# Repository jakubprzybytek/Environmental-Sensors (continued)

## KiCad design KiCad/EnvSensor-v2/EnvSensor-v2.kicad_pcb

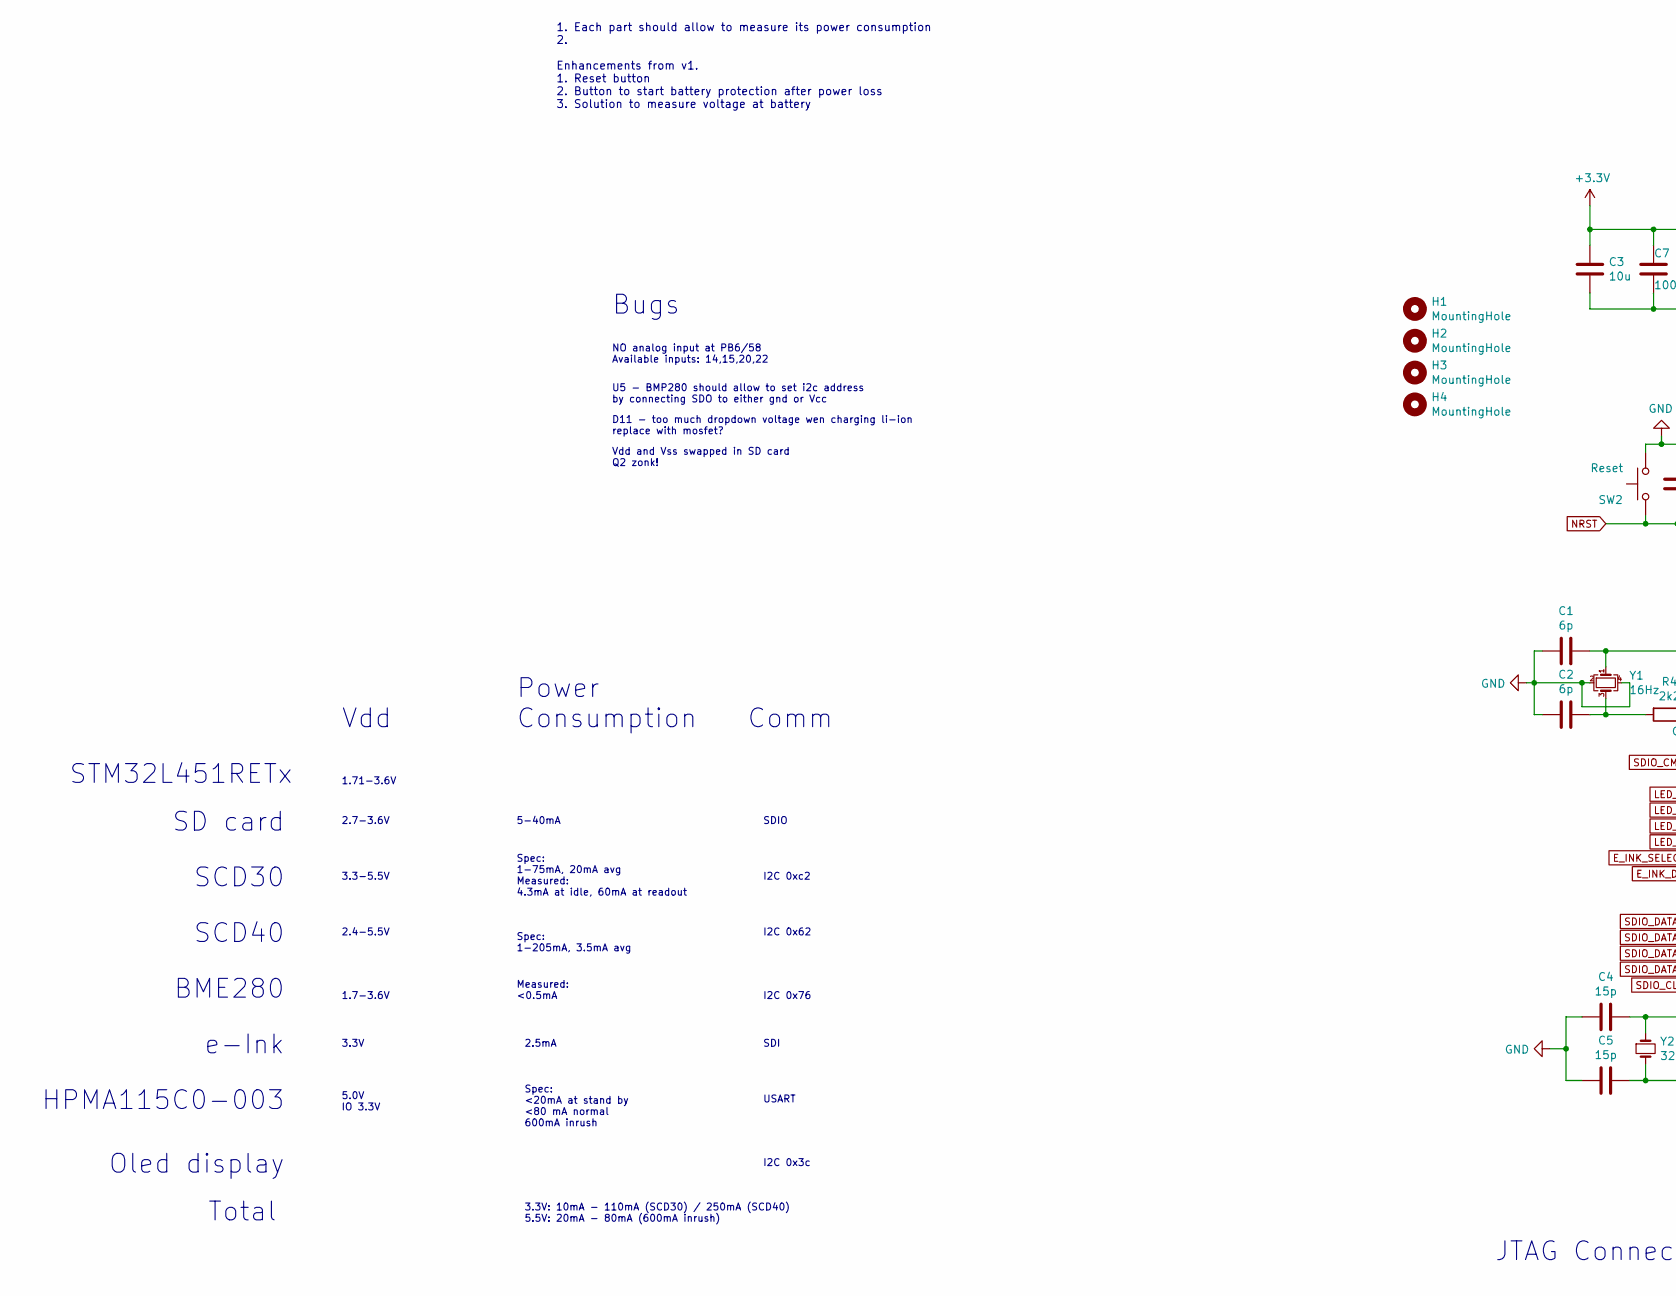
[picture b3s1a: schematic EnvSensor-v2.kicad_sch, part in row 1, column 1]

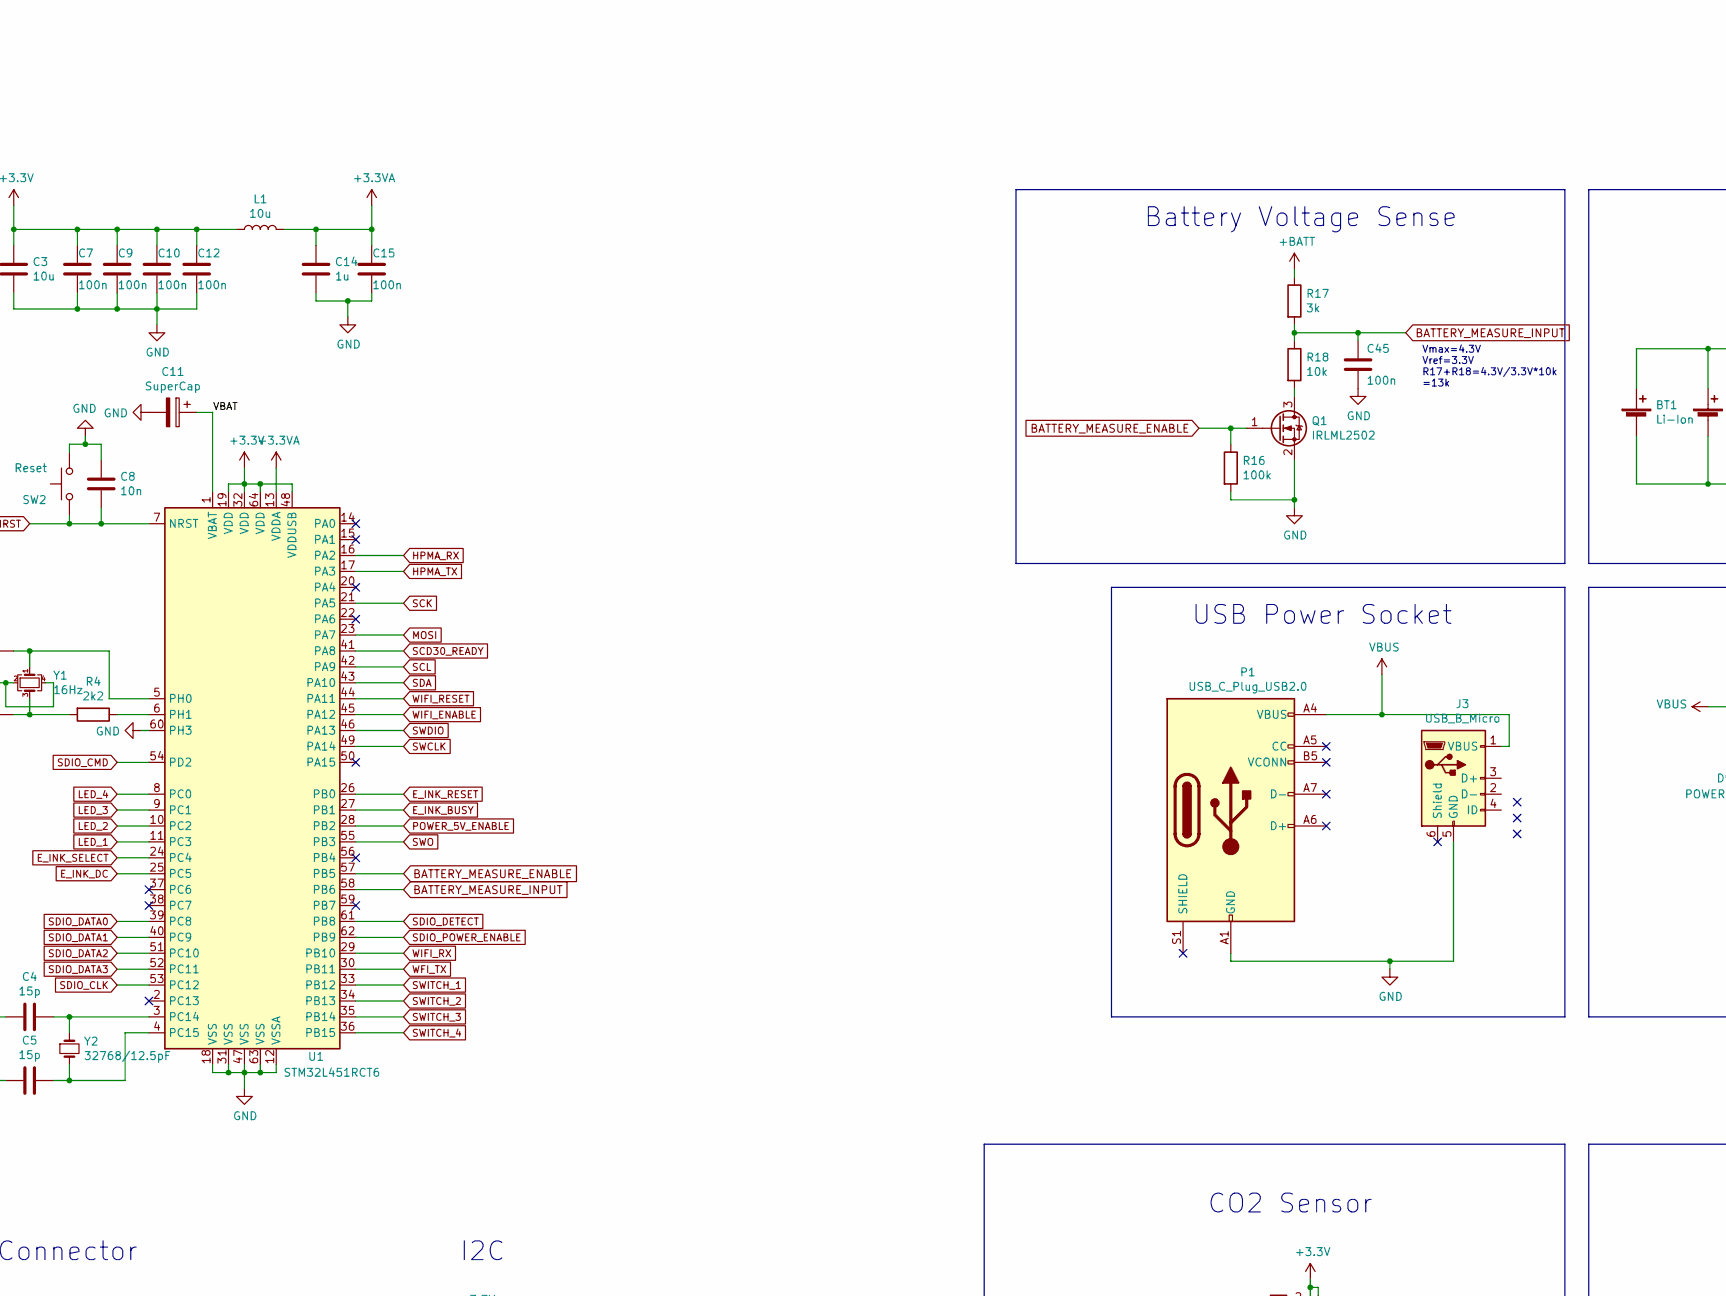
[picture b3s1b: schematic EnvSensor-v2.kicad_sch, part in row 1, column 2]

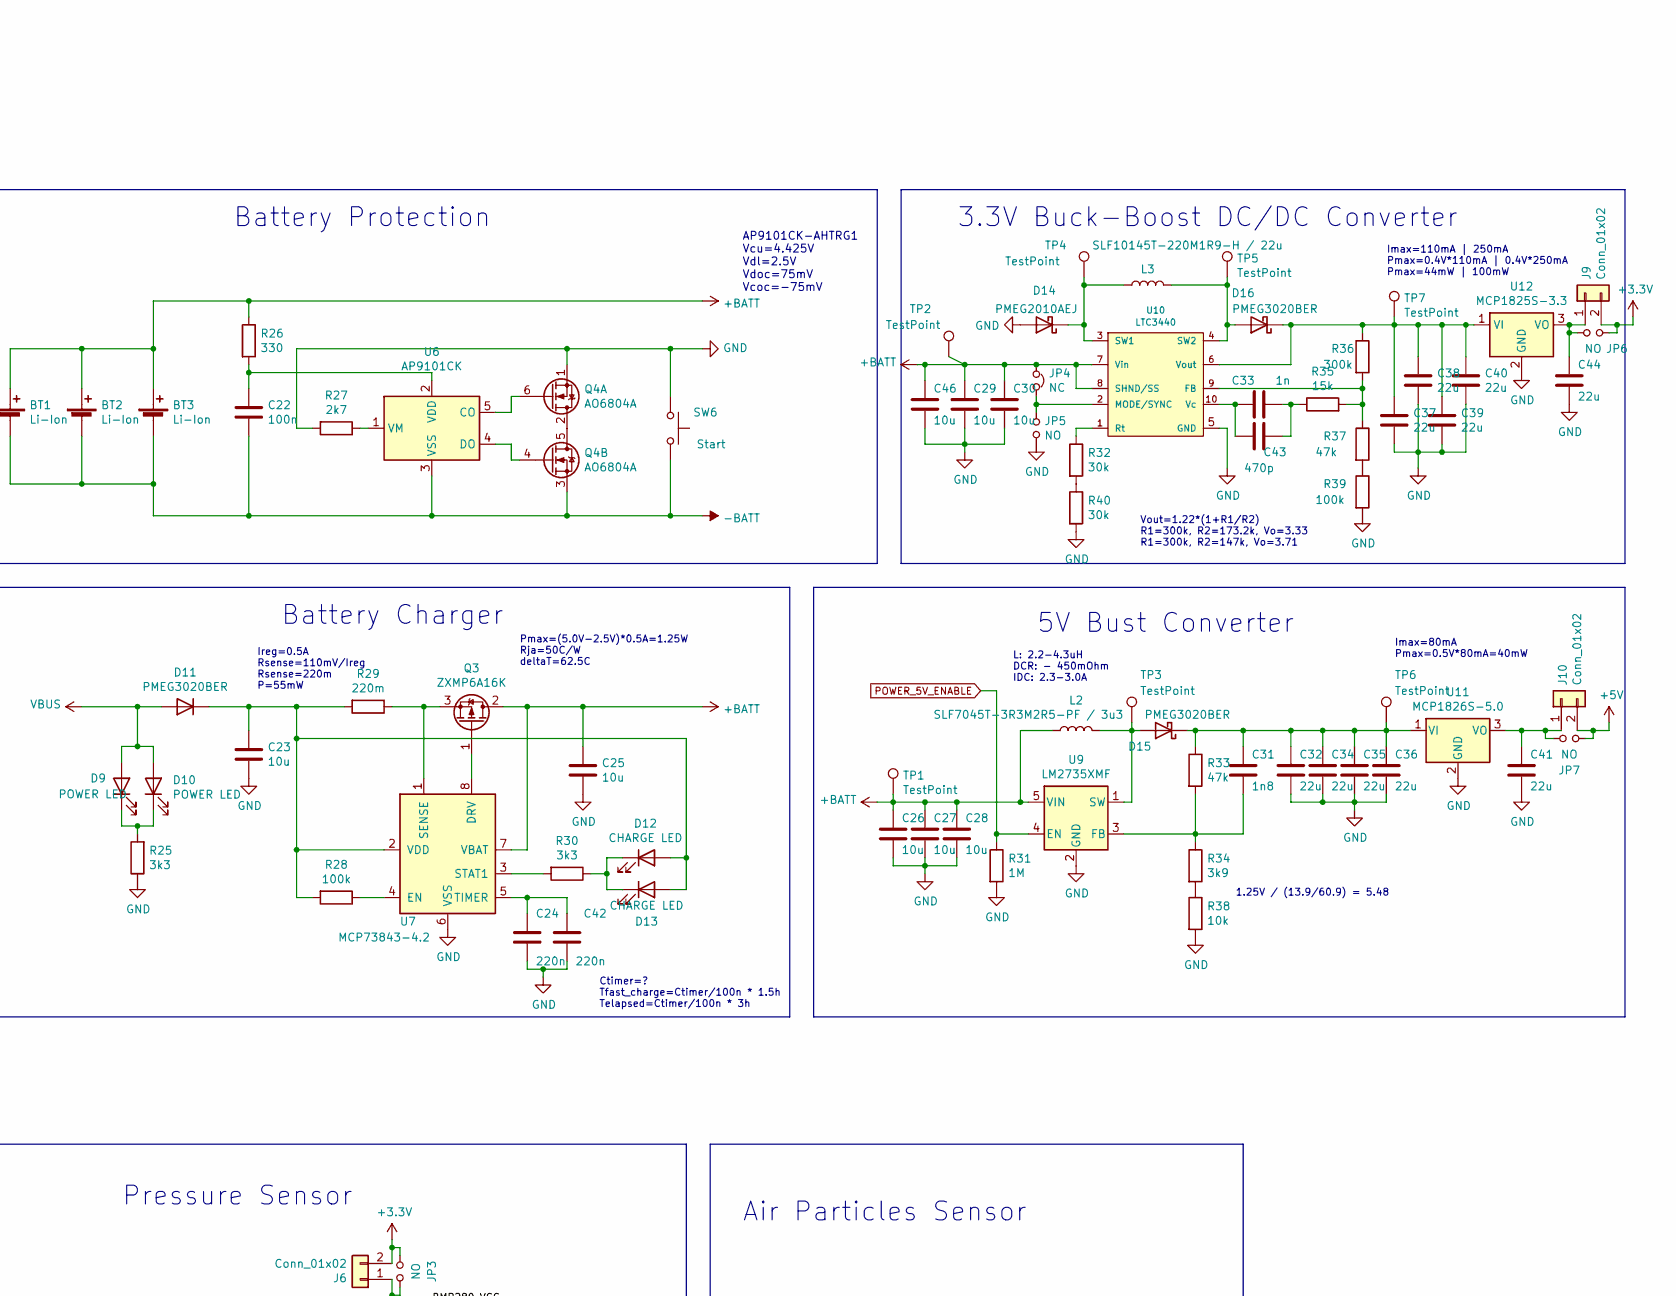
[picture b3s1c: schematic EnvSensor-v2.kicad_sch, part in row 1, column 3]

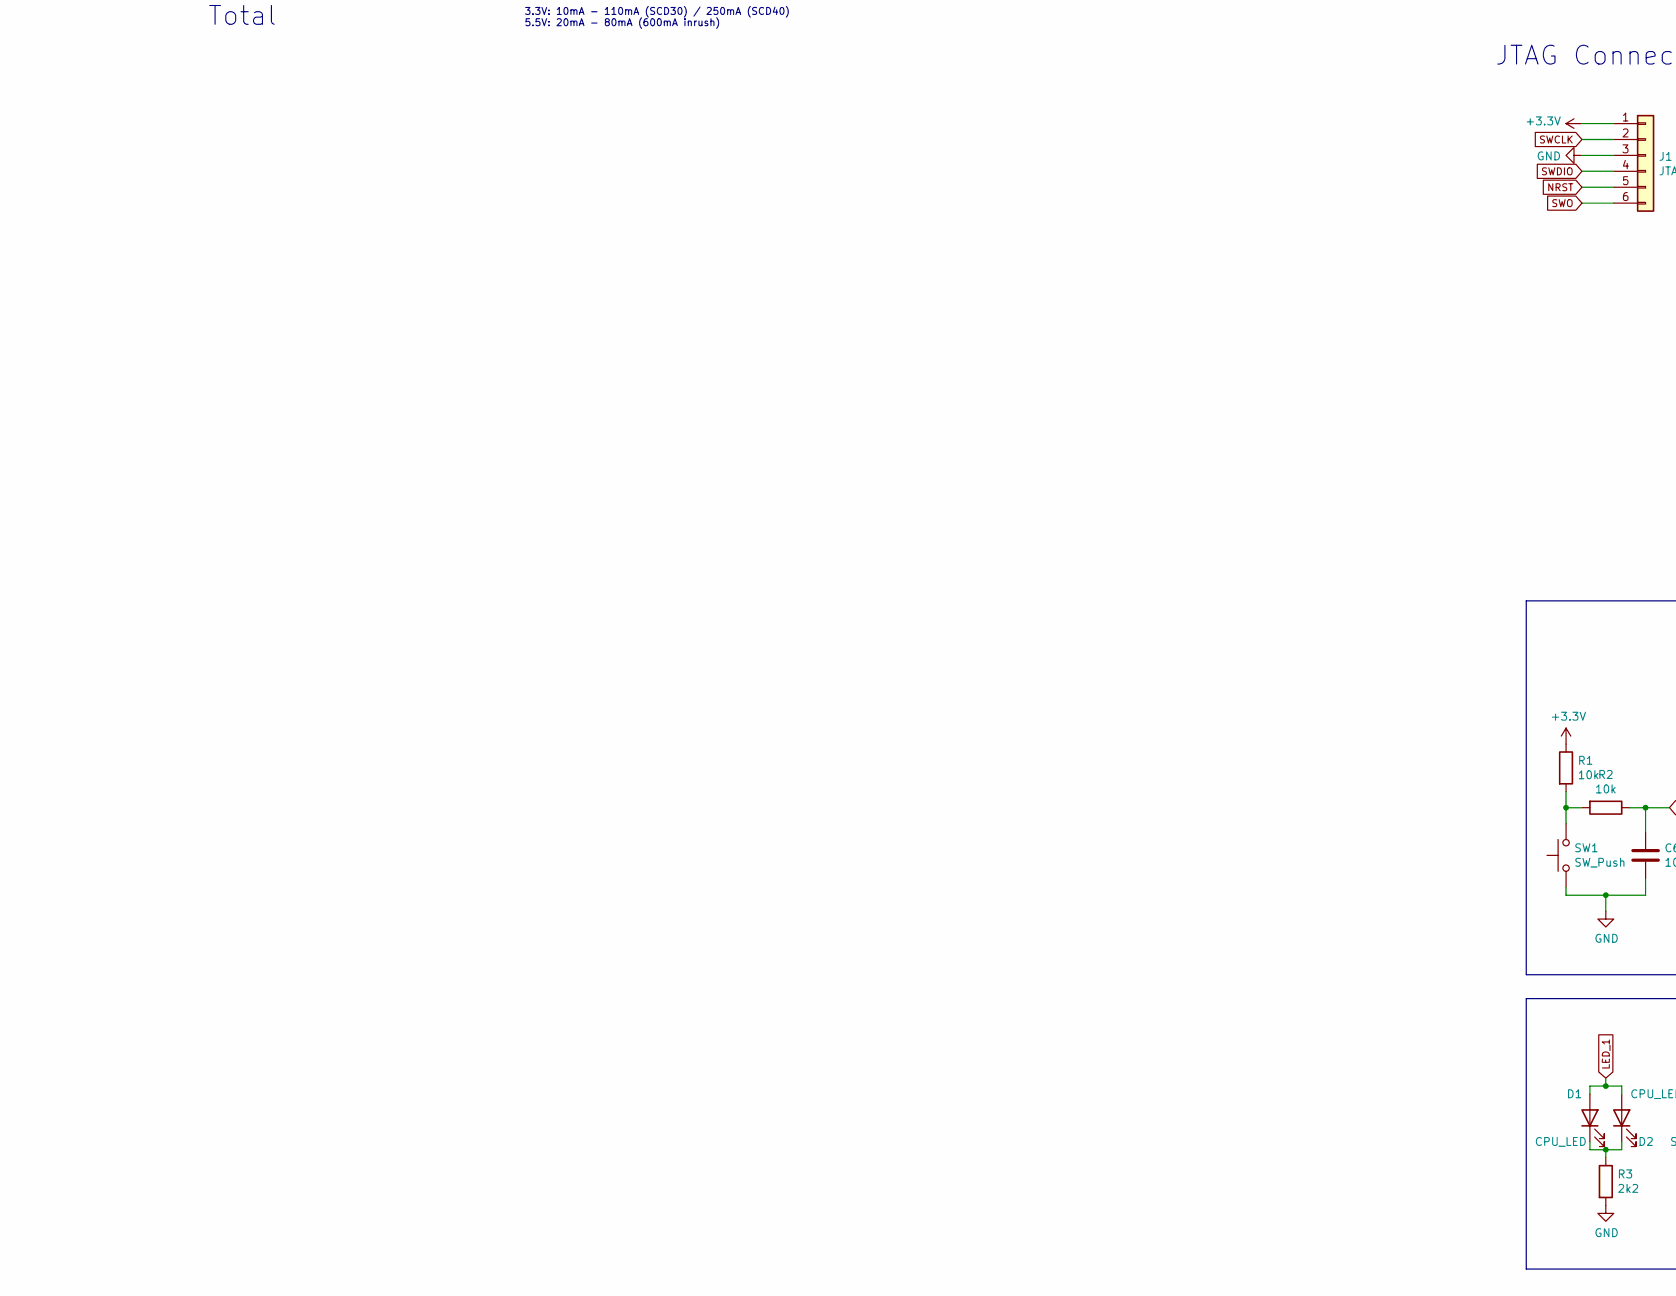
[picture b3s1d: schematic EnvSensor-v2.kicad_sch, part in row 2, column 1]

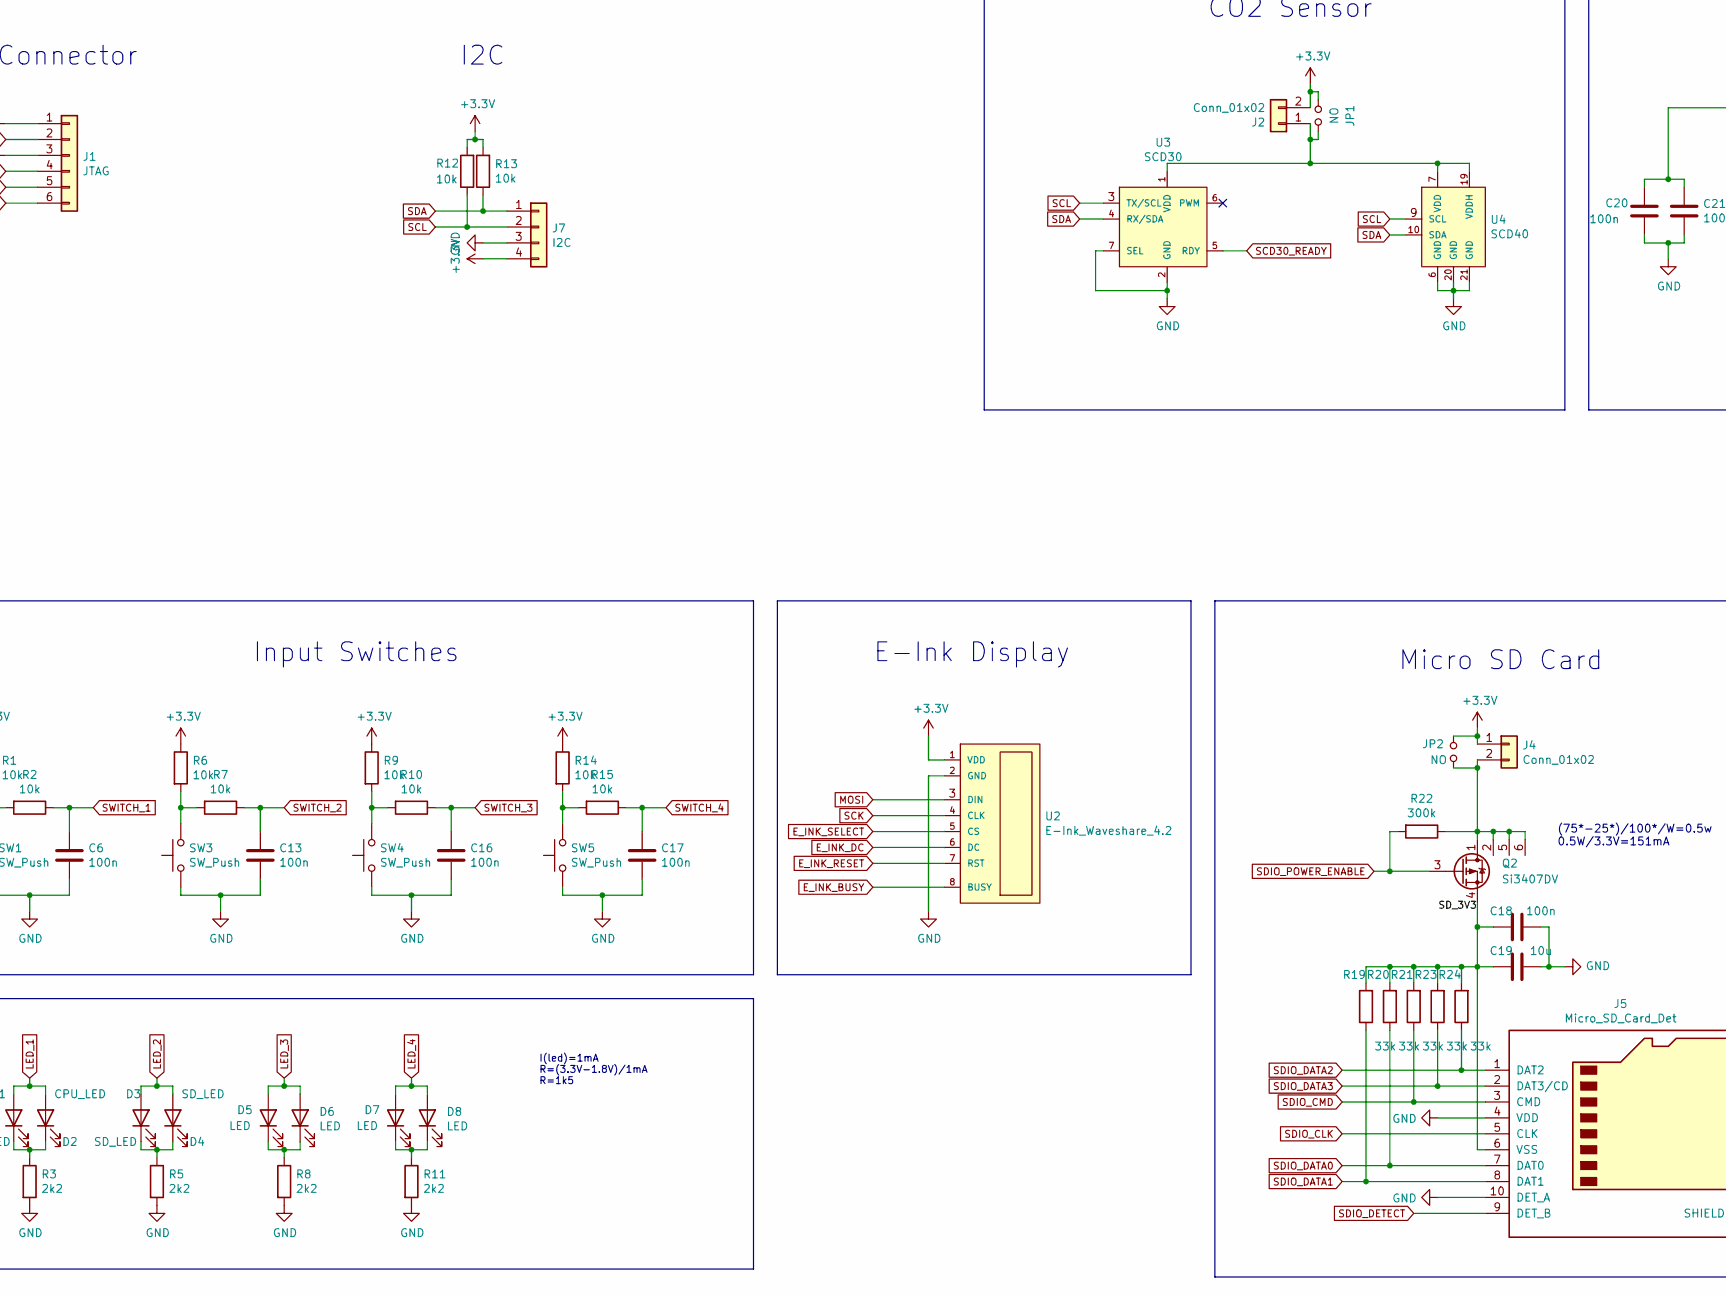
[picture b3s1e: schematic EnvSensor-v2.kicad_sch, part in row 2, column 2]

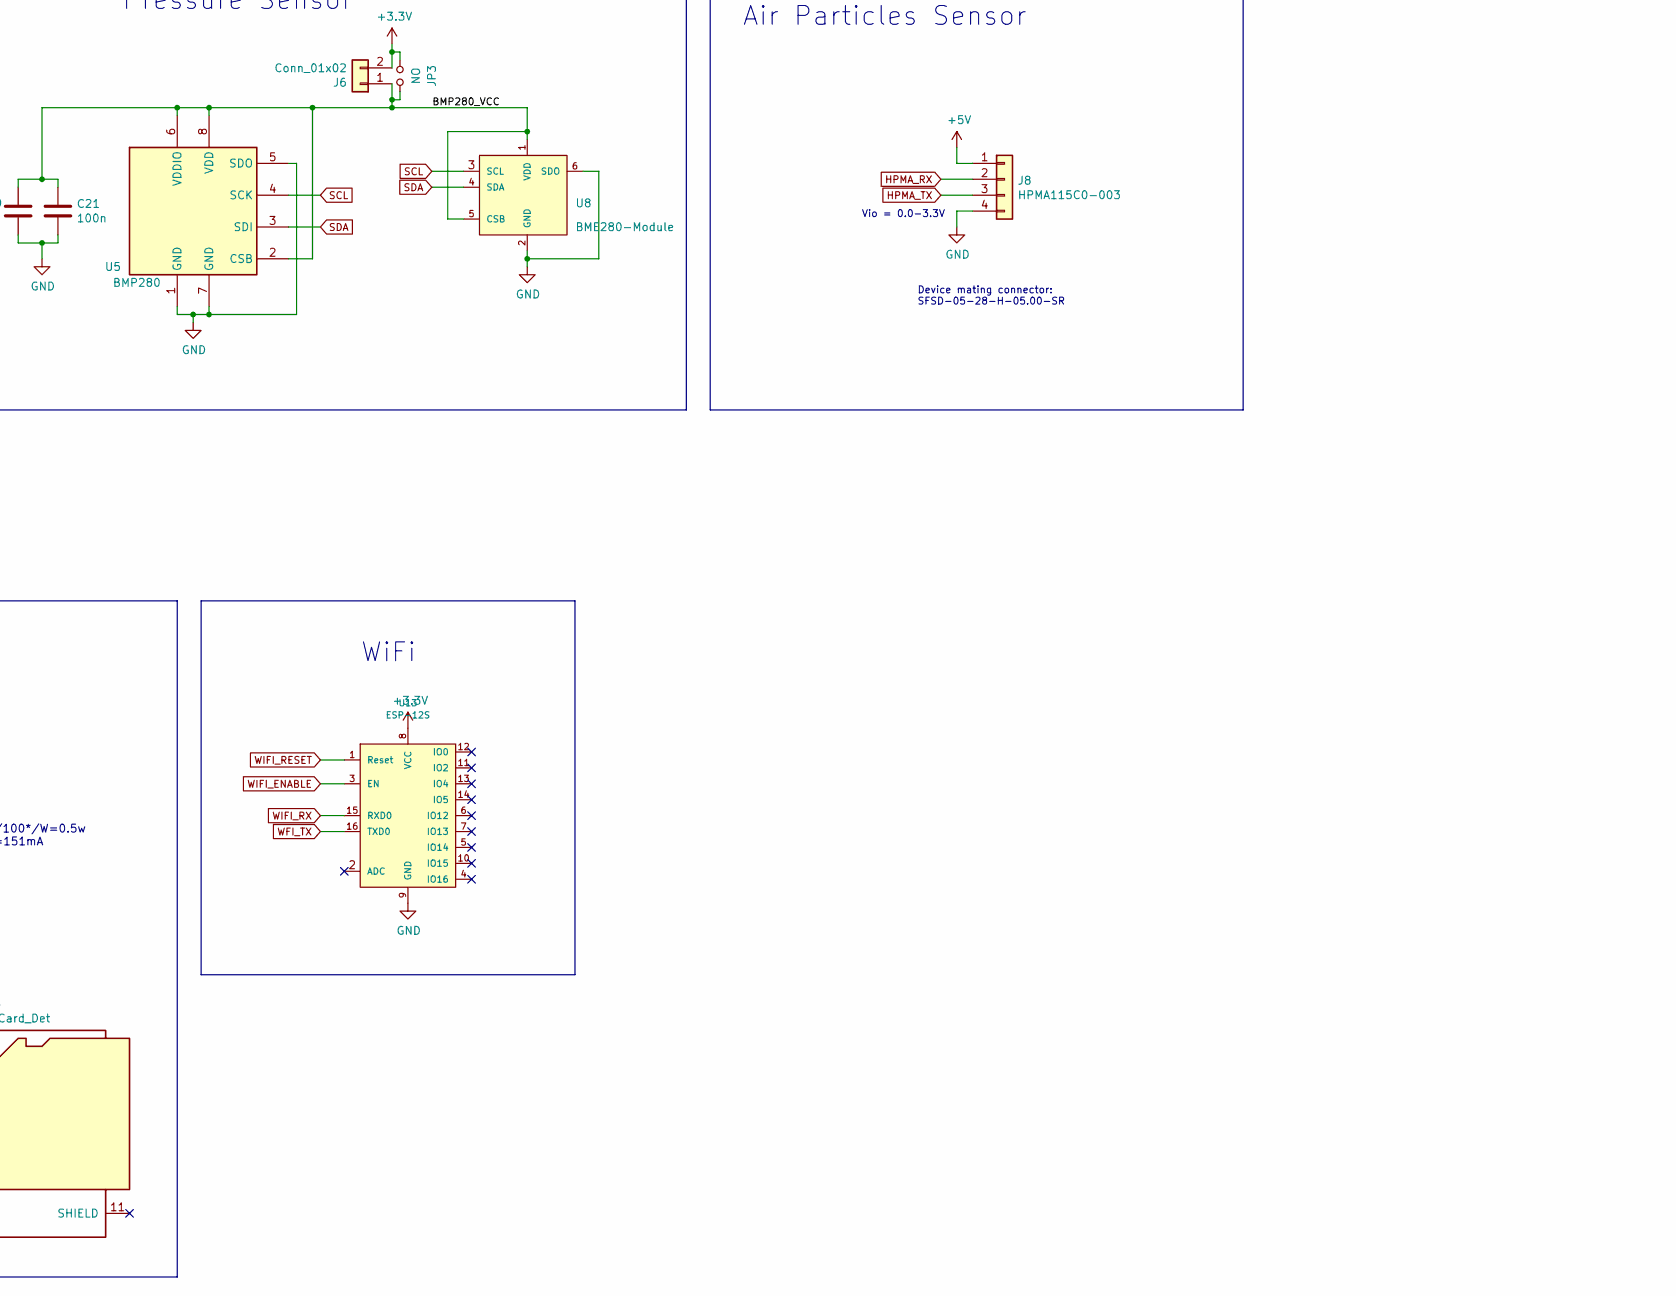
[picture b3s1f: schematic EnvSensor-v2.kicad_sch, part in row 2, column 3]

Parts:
BT1, BT2, BT3: Li-Ion; BatteryHolder_Keystone_1042_1x18650
C1, C2: 6p; C_0805_2012Metric
C3, C19, C23, C25, C26, C27, C28, C29, C30, C46: 10u; C_0805_2012Metric
C4, C5: 15p; C_0805_2012Metric
C6, C7, C9, C10, C12, C13, C15, C16, C17, C18, C20, C21, C22: 100n; C_0603_1608Metric
C8: 10n; C_0805_2012Metric
C11: SuperCap; CP_Elec_10x7.7
C14: 1u; C_0805_2012Metric
C24, C42: 220n; C_0805_2012Metric
C31: 1n8; C_0805_2012Metric
C32, C34, C35, C36, C37, C38, C39, C40, C41, C44: 22u; C_1206_3216Metric
C33: 1n; C_0805_2012Metric
C43: 470p; C_0805_2012Metric
C45: 100n; C_0805_2012Metric
D1: CPU_LED; LED_0805_2012Metric
D2: CPU_LED; LED_D3.0mm
D3: SD_LED; LED_0805_2012Metric
D4: SD_LED; LED_D3.0mm
D5, D7: LED; LED_0805_2012Metric
D6, D8: LED; LED_D3.0mm
D9: POWER LED; LED_0805_2012Metric
D10: POWER LED; LED_D3.0mm_Horizontal_O3.81mm_Z6.0mm
D11, D15, D16: PMEG3020BER; D_SOD-123
D12: CHARGE LED; LED_0805_2012Metric
D13: CHARGE LED; LED_D3.0mm_Horizontal_O3.81mm_Z6.0mm
D14: PMEG2010AEJ; D_SOD-323_HandSoldering
H1, H2, H3, H4: MountingHole; MountingHole_3.2mm_M3
J1: JTAG; PinHeader_1x06_P2.54mm_Vertical
J2, J4, J6, J9, J10: Conn_01x02; PinHeader_1x02_P2.54mm_Vertical
J3: USB_B_Micro; USB_Micro-B_Molex_47346-0001
J5: Micro_SD_Card_Det; microSD_HC_Hirose_DM3AT-SF-PEJM5
J7: I2C; PinSocket_1x04_P2.54mm_Vertical
J8: HPMA115C0-003; PinHeader_1x04_P2.54mm_Vertical
JP1, JP2, JP3, JP5, JP6, JP7: NO; SolderJumper-2_P1.3mm_Open_RoundedPad1.0x1.5mm
JP4: NC; SolderJumper-2_P1.3mm_Bridged_RoundedPad1.0x1.5mm
L1: 10u; L_0805_2012Metric
L2: SLF7045T-3R3M2R5-PF / 3u3; L_TDK_SLF7045
L3: SLF10145T-220M1R9-H / 22u; L_TDK_SLF10145
P1: USB_C_Plug_USB2.0; USB_C_Receptacle_Adam_Tech
Q1: IRLML2502; SOT-23
Q2: Si3407DV; TSOT-23-6
Q3: ZXMP6A16K; TO-252-2
Q4: AO6804A; TSOT-23-6
R1, R2, R6, R7, R9, R10, R14, R15: 10k; R_0603_1608Metric
R3, R4, R5, R8, R11: 2k2; R_0805_2012Metric
R12, R13, R18, R38: 10k; R_0805_2012Metric
R16, R39: 100k; R_0805_2012Metric
R17: 3k; R_0805_2012Metric
R19, R20, R21, R23, R24: 33k; R_0805_2012Metric
R22, R36: 300k; R_0805_2012Metric
R25, R30: 3k3; R_0805_2012Metric
R26: 330; R_0805_2012Metric
R27: 2k7; R_0805_2012Metric
R28: 100k; R_0603_1608Metric
R29: 220m; R_1206_3216Metric
R31: 1M; R_0805_2012Metric
R32, R40: 30k; R_0805_2012Metric
R33, R37: 47k; R_0805_2012Metric
R34: 3k9; R_0805_2012Metric
R35: 15k; R_0805_2012Metric
SW1, SW3, SW4, SW5: SW_Push; SW_SPST_PTS645
SW2: Reset; SW_Tactile_SKHH_Angled
SW6: Start; SW_SPST_CK_RS282G05A3
TP1, TP2, TP3, TP4, TP5, TP6, TP7: TestPoint; TestPoint_THTPad_D1.5mm_Drill0.7mm
U1: STM32L451RCT6; LQFP-64_10x10mm_P0.5mm
U2: E-Ink_Waveshare_4.2; 4.2inch_E-Ink
U3: SCD30
U4: SCD40; SCD4x
U5: BMP280; Bosch_LGA-8_2.5x2.5mm_P0.65mm_ClockwisePinNumbering
U6: AP9101CK; SOT-23-5
U7: MCP73843-4.2; MSOP-8_3x3mm_P0.65mm
U8: BME280-Module
U9: LM2735XMF; SOT-23-5
U10: LTC3440; MSOP-10_3x3mm_P0.5mm
U11: MCP1826S-5.0; SOT-223-3_TabPin2
U12: MCP1825S-3.3; SOT-223-3_TabPin2
U13: ESP-12S
Y1: 16Hz; Crystal_SMD_Abracon_ABM3B-4Pin_5.0x3.2mm
Y2: 32768/12.5pF; Crystal_SMD_MicroCrystal_CC7V-T1A-2Pin_3.2x1.5mm

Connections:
+3.3VA: C14.1, C15.1, L1.2, U1.13 (VDDA)
+3V3: C3.1, C7.1, C9.1, C10.1, C12.1, J1.1, J2.2, J4.1, J6.2, J7.4, J9.2, JP1.2, JP2.1, JP3.2, JP6.2, L1.1, R1.1, R6.1, R9.1, R12.2, R13.2, R14.1, U1.19 (VDD), U1.32 (VDD), U1.48 (VDDUSB), U1.64 (VDD), U2.1 (VDD), U13.8 (VCC)
+5V: J8.1, J10.2, JP7.2
+BATT: BT1.1 (+), BT2.1 (+), BT3.1 (+), C25.1, C26.1, C27.1, C28.1, C29.1, C30.1, C46.1, JP4.1, L2.1, Q3.2 (D), R17.1, R26.1, TP1.1, TP2.1, U7.7 (VBAT), U9.5 (VIN), U10.7 (Vin), U10.8 (SHND/SS)
-BATT: BT1.2 (-), BT2.2 (-), BT3.2 (-), C22.2, Q4.3 (S2), SW6.1, U6.3 (VSS)
/BMP280_VCC: C20.1, C21.1, J6.1, JP3.1, U5.2 (CSB), U5.6 (VDDIO), U5.8 (VDD), U8.1 (VDD), U8.5 (CSB)
/SD_3V3: C18.2, C19.2, J5.6 (VSS), Q2.4 (S), R19.2, R20.2, R21.2, R23.2, R24.2
/VBAT: C11.1, U1.1 (VBAT)
BATTERY_MEASURE_ENABLE: Q1.1 (G), R16.1, U1.57 (PB5)
BATTERY_MEASURE_INPUT: C45.1, R17.2, R18.1, U1.58 (PB6)
E_INK_BUSY: U1.27 (PB1), U2.8 (BUSY)
E_INK_DC: U1.25 (PC5), U2.6 (DC)
E_INK_RESET: U1.26 (PB0), U2.7 (RST)
E_INK_SELECT: U1.24 (PC4), U2.5 (CS)
GND: C1.2, C2.2, C3.2, C4.2, C5.2, C6.2, C7.2, C8.1, C9.2, C10.2, C11.2, C12.2, C13.2, C14.2, C15.2, C16.2, C17.2, C18.1, C19.1, C20.2, C21.2, C23.2, C24.2, C25.2, C26.2, C27.2, C28.2, C29.2, C30.2, C32.2, C34.2, C35.2, C36.2, C37.2, C38.2, C39.2, C40.2, C41.2, C42.2, C44.2, C45.2, C46.2, D14.2 (A), J1.3, J3.5 (GND), J5.4 (VDD), J5.10 (DET_A), J7.3, J8.4, JP5.2, P1.A1 (GND), P1.A12 (GND), P1.B1 (GND), P1.B12 (GND), Q1.2 (S), Q4.1 (S2), R3.2, R5.2, R8.2, R11.2, R16.2, R25.1, R27.2, R31.2, R38.2, R39.2, R40.2, SW1.1, SW2.1, SW3.1, SW4.1, SW5.1, SW6.2, U1.12 (VSSA), U1.18 (VSS), U1.31 (VSS), U1.47 (VSS), U1.60 (PH3), U1.63 (VSS), U2.2 (GND), U3.2 (GND), U3.7 (SEL), U4.6 (GND), U4.20 (GND), U4.21 (GND), U5.1 (GND), U5.5 (SDO), U5.7 (GND), U7.6 (VSS), U8.2 (GND), U8.6 (SDO), U9.2 (GND), U10.5 (GND), U11.2 (GND), U12.2 (GND), U13.9 (GND), Y1.2, Y1.4
HPMA_RX: J8.2, U1.16 (PA2)
HPMA_TX: J8.3, U1.17 (PA3)
LED_1: D1.2 (A), D2.2 (A), U1.11 (PC3)
LED_2: D3.2 (A), D4.2 (A), U1.10 (PC2)
LED_3: D5.2 (A), D6.2 (A), U1.9 (PC1)
LED_4: D7.2 (A), D8.2 (A), U1.8 (PC0)
MOSI: U1.23 (PA7), U2.3 (DIN)
NRST: C8.2, J1.5, SW2.2, U1.7 (NRST)
unnamed: C1.1, U1.5 (PH0), Y1.1
unnamed: C2.1, R4.2, Y1.3
unnamed: C4.1, U1.3 (PC14), Y2.1
unnamed: C5.1, U1.4 (PC15), Y2.2
unnamed: C22.1, R26.2, U6.2 (VDD)
unnamed: C23.1, D11.1 (K), D12.2 (A), D13.2 (A), R28.2, R29.2, U7.2 (VDD)
unnamed: C24.1, C42.1, U7.5 (TIMER)
unnamed: C31.1, C32.1, C34.1, C35.1, C36.1, D15.1 (K), R33.1, TP6.1, U11.1 (VI)
unnamed: C31.2, R33.2, R34.1, U9.3 (FB)
unnamed: C33.1, C43.1, R35.1
unnamed: C33.2, C43.2, U10.10 (Vc)
unnamed: C37.1, C38.1, C39.1, C40.1, D16.1 (K), R36.1, TP7.1, U10.6 (Vout), U12.1 (VI)
unnamed: C41.1, J10.1, JP7.1, U11.3 (VO)
unnamed: C44.1, J9.1, JP6.1, U12.3 (VO)
unnamed: D1.1 (K), D2.1 (K), R3.1
unnamed: D3.1 (K), D4.1 (K), R5.1
unnamed: D5.1 (K), D6.1 (K), R8.1
unnamed: D7.1 (K), D8.1 (K), R11.1
unnamed: D9.1 (K), D10.1 (K), R25.2
unnamed: D12.1 (K), D13.1 (K), R30.1
unnamed: D14.1 (K), L3.1, TP4.1, U10.3 (SW1)
unnamed: D15.2 (A), L2.2, TP3.1, U9.1 (SW)
unnamed: D16.2 (A), L3.2, TP5.1, U10.4 (SW2)
unnamed: J2.1, JP1.1, U3.1 (VDD), U4.7 (VDD), U4.19 (VDDH)
unnamed: J4.2, JP2.2, Q2.1 (D), Q2.2 (D), Q2.5 (D), Q2.6 (D), R22.1
unnamed: JP4.2, JP5.1, U10.2 (MODE/SYNC)
unnamed: Q1.3 (D), R18.2
unnamed: Q3.1 (G), U7.8 (DRV)
unnamed: Q3.3 (S), R29.1, U7.1 (SENSE)
unnamed: Q4.2 (D2), Q4.5 (D2)
unnamed: Q4.4 (G2), U6.4 (DO)
unnamed: Q4.6 (G2), U6.5 (CO)
unnamed: R1.2, R2.2, SW1.2
unnamed: R4.1, U1.6 (PH1)
unnamed: R6.2, R7.2, SW3.2
unnamed: R9.2, R10.2, SW4.2
unnamed: R14.2, R15.2, SW5.2
unnamed: R27.1, U6.1 (VM)
unnamed: R28.1, U7.4 (EN)
unnamed: R30.2, U7.3 (STAT1)
unnamed: R32.1, U10.1 (Rt)
unnamed: R32.2, R40.1
unnamed: R34.2, R38.1
unnamed: R35.2, R36.2, R37.1, U10.9 (FB)
unnamed: R37.2, R39.1
POWER_5V_ENABLE: R31.1, U1.28 (PB2), U9.4 (EN)
SCD30_READY: U1.41 (PA8), U3.5 (RDY)
SCK: U1.21 (PA5), U2.4 (CLK)
SCL: J7.2, R12.1, U1.42 (PA9), U3.3 (TX/SCL), U4.9 (SCL), U5.4 (SCK), U8.3 (SCL)
SDA: J7.1, R13.1, U1.43 (PA10), U3.4 (RX/SDA), U4.10 (SDA), U5.3 (SDI), U8.4 (SDA)
SDIO_CLK: J5.5 (CLK), U1.53 (PC12)
SDIO_CMD: J5.3 (CMD), R21.1, U1.54 (PD2)
SDIO_DATA0: J5.7 (DAT0), R20.1, U1.39 (PC8)
SDIO_DATA1: J5.8 (DAT1), R19.1, U1.40 (PC9)
SDIO_DATA2: J5.1 (DAT2), R24.1, U1.51 (PC10)
SDIO_DATA3: J5.2 (DAT3/CD), R23.1, U1.52 (PC11)
SDIO_DETECT: J5.9 (DET_B), U1.61 (PB8)
SDIO_POWER_ENABLE: Q2.3 (G), R22.2, U1.62 (PB9)
SWCLK: J1.2, U1.49 (PA14)
SWDIO: J1.4, U1.46 (PA13)
SWITCH_1: C6.1, R2.1, U1.33 (PB12)
SWITCH_2: C13.1, R7.1, U1.34 (PB13)
SWITCH_3: C16.1, R10.1, U1.35 (PB14)
SWITCH_4: C17.1, R15.1, U1.36 (PB15)
SWO: J1.6, U1.55 (PB3)
VBUS: D9.2 (A), D10.2 (A), D11.2 (A), J3.1 (VBUS), P1.A4 (VBUS), P1.A9 (VBUS), P1.B4 (VBUS), P1.B9 (VBUS)
WFI_TX: U1.30 (PB11), U13.16 (TXD0)
WIFI_ENABLE: U1.45 (PA12), U13.3 (EN)
WIFI_RESET: U1.44 (PA11), U13.1 (Reset)
WIFI_RX: U1.29 (PB10), U13.15 (RXD0)

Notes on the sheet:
Micro SD Card
e-Ink
L: 2.2-4.3uH DCR: - 450mOhm IDC: 2.3-3.0A
AP9101CK-AHTRG1 Vcu=4.425V Vdl=2.5V Vdoc=75mV Vcoc=-75mV
I2C 0x76
I2C 0x62
3.3-5.5V
D11 - too much dropdown voltage wen charging li-ion replace with mosfet?
1. Each part should allow to measure its power consumption 2. Enhancements from v1. 1. Reset button 2. Button to start battery protection after power loss 3. Solution to measure voltage at battery
Battery Charger
Vdd and Vss swapped in SD card Q2 zonk!
Vmax=4.3V Vref=3.3V R17+R18=4.3V/3.3V*10k =13k
SDIO
WiFi
CO2 Sensor
Measured: <0.5mA
5V Bust Converter
Ireg=0.5A Rsense=110mV/Ireg Rsense=220m P=55mW
Total
1.71-3.6V
SD card
I2C
Pmax=(5.0V-2.5V)*0.5A=1.25W Rja=50C/W deltaT=62.5C
Input Switches
Pressure Sensor
SDI
3.3V: 10mA - 110mA (SCD30) / 250mA (SCD40) 5.5V: 20mA - 80mA (600mA inrush)
5-40mA
Power Consumption
Device mating connector: SFSD-05-28-H-05.00-SR
3.3V Buck-Boost DC/DC Converter
SCD40
E-Ink Display
2.7-3.6V
2.5mA
Imax=110mA | 250mA Pmax=0.4V*110mA | 0.4V*250mA Pmax=44mW | 100mW
Battery Voltage Sense
5.0V IO 3.3V
USB Power Socket
I2C 0x3c

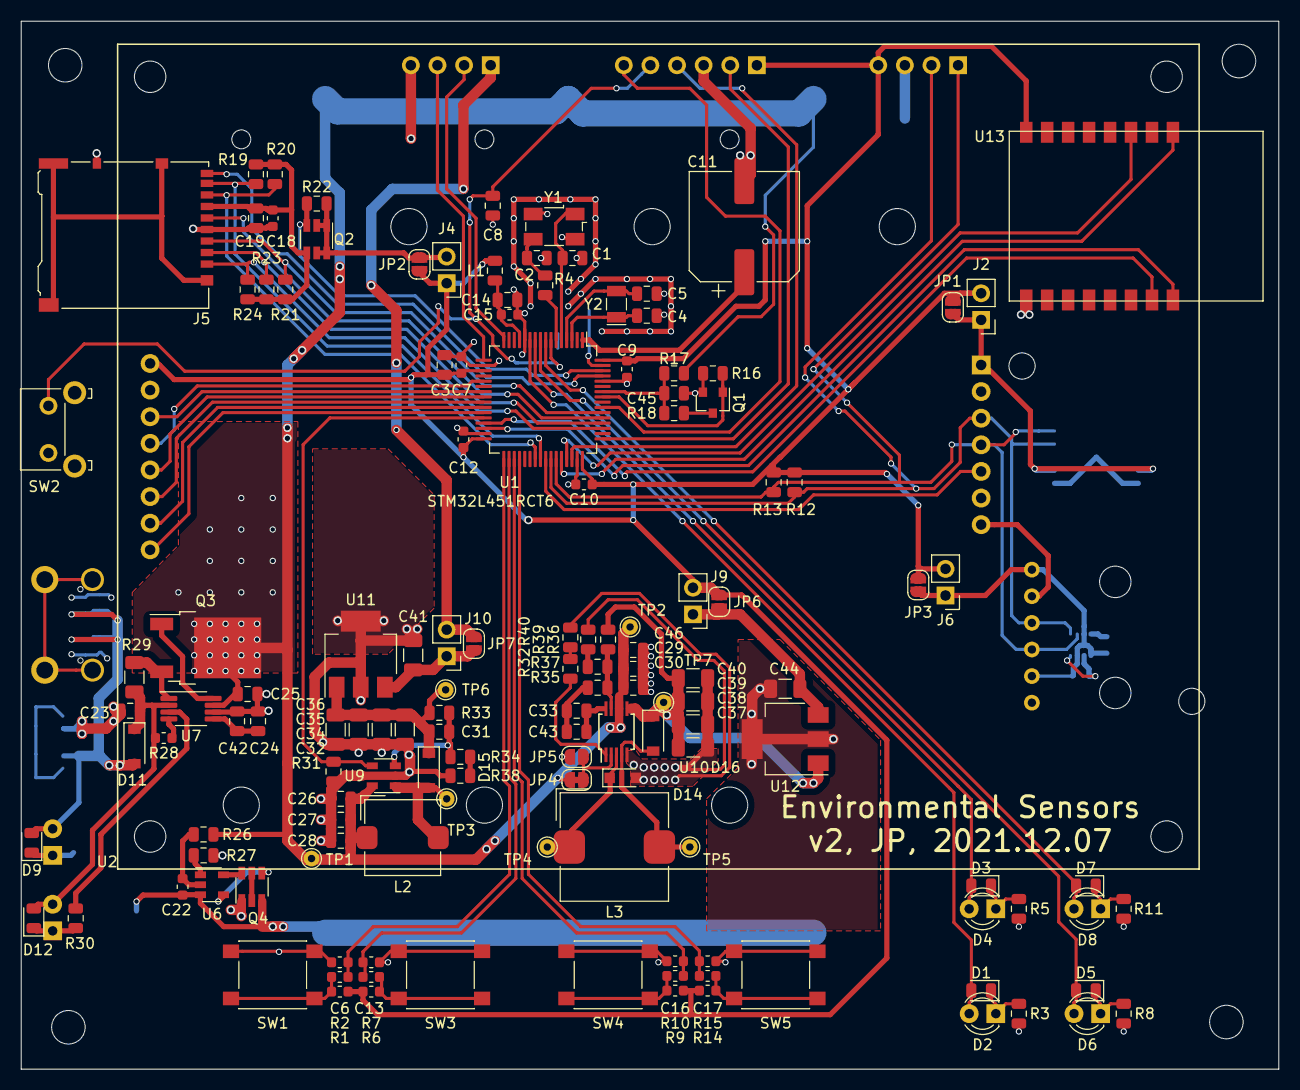
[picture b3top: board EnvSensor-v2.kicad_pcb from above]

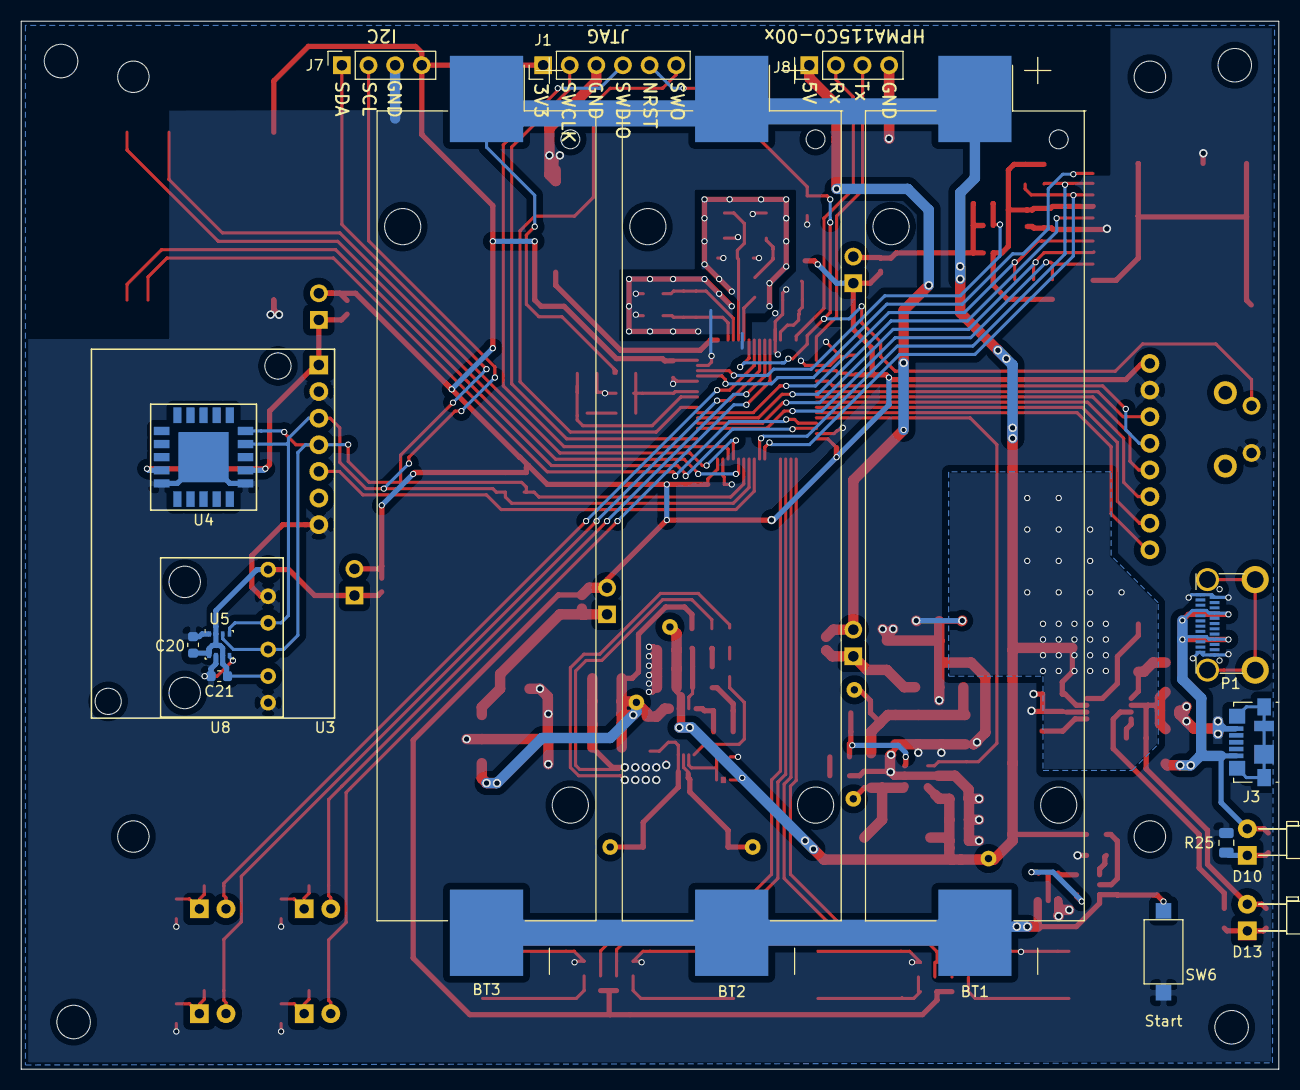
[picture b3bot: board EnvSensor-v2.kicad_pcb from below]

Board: 2 copper layers, 120.0 x 100.0 mm, 162 parts (18 on the bottom side), 93 nets.
